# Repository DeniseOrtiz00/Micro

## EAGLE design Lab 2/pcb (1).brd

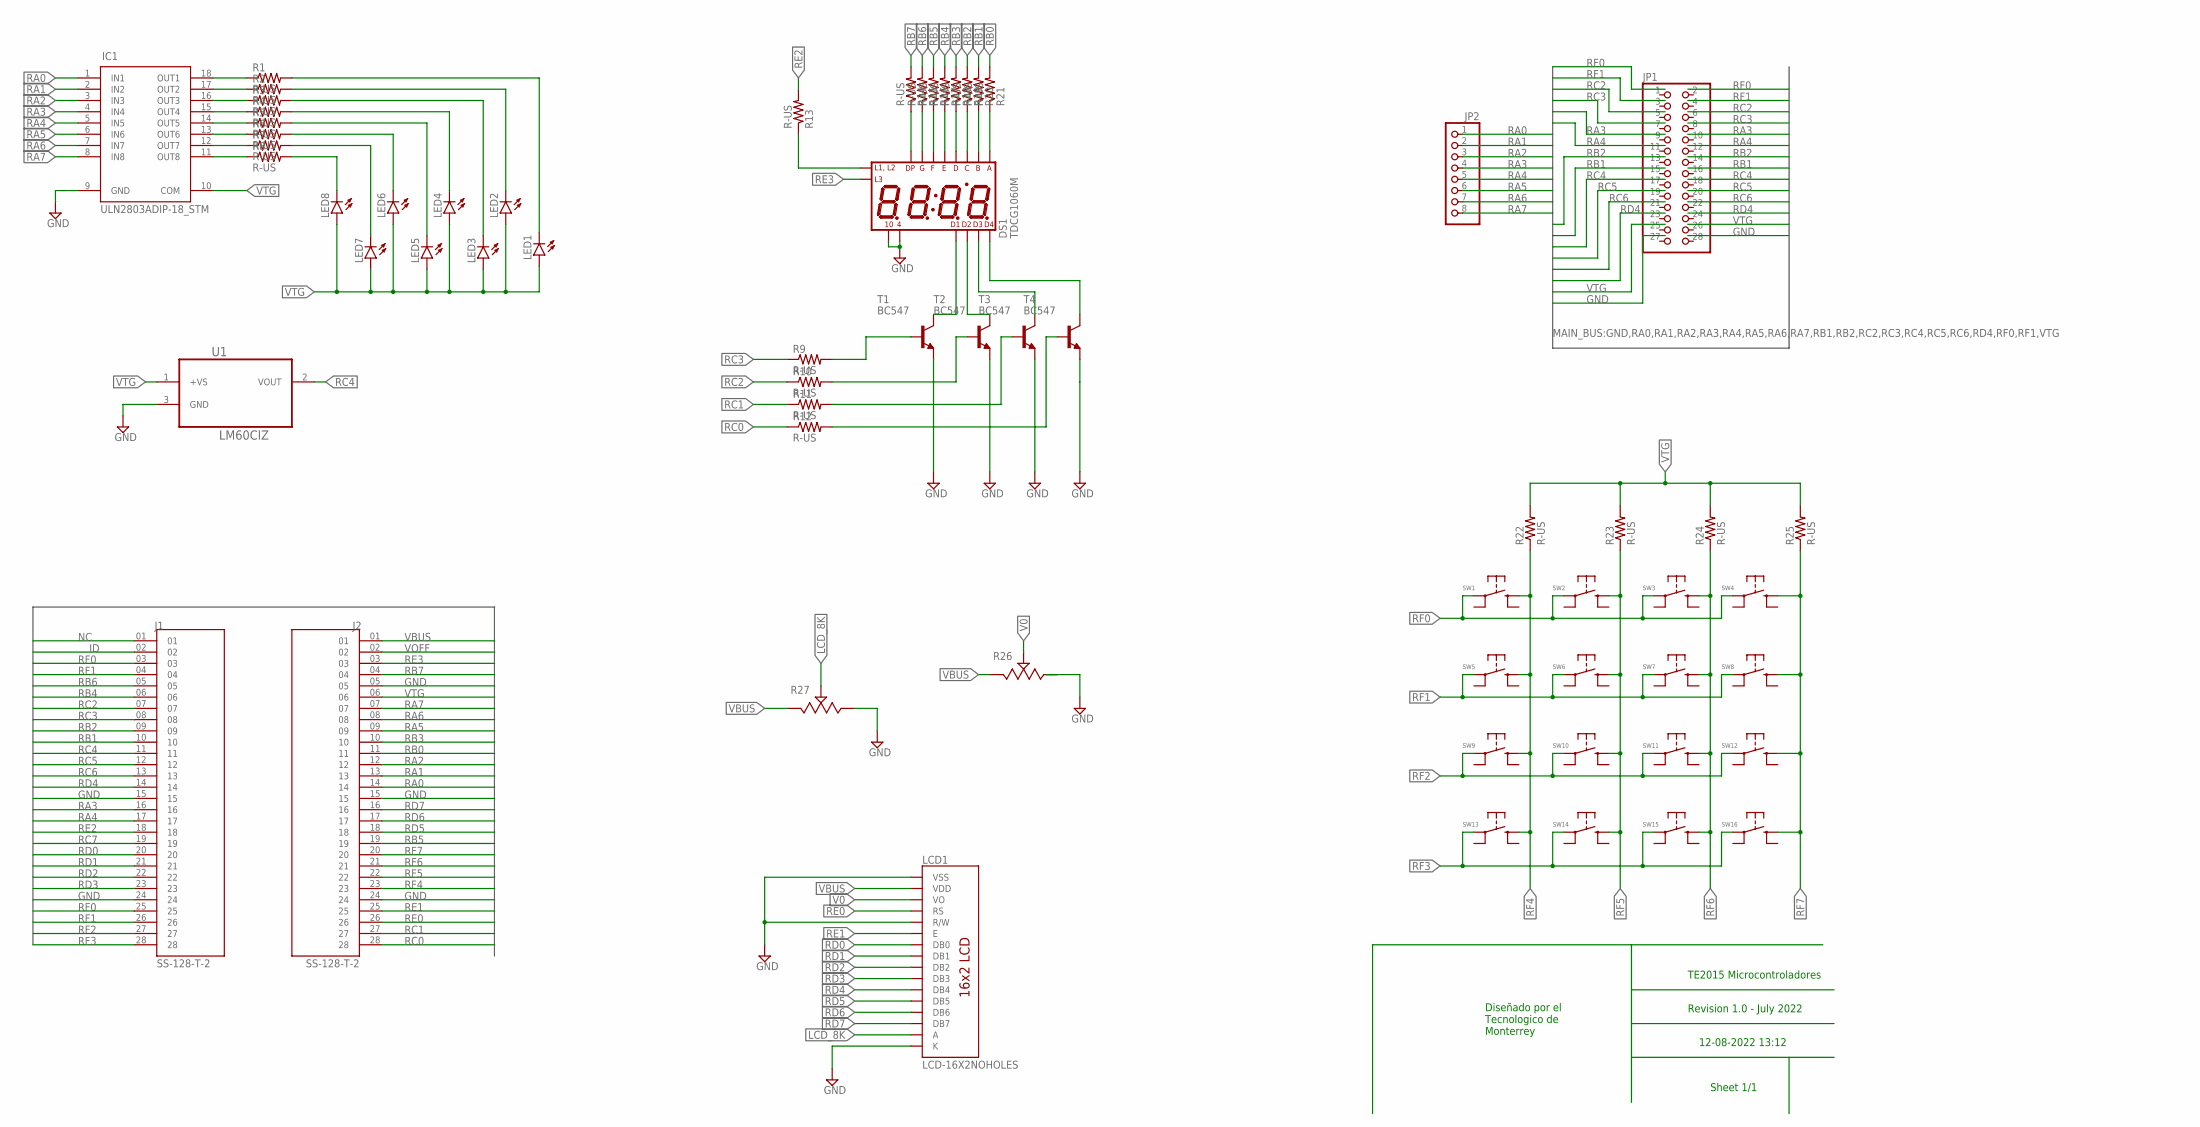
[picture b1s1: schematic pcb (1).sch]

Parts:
DS1: TDCG1060M; DISPLAY_TDCG1060M
IC1: ULN2803ADIP-18_STM; DIP-18_STM
J1, J2: SS-128-T-2; SAMTEC_SS-128-T-2
JP1: PINHD-2X14-CB; 2X14-BIG
JP2: PINHD-1X8BIG; 1X08-BIG
LCD1: LCD-16X2NOHOLES; LCD-16X2_NOHOLESNOSILK
LED1, LED2, LED3, LED4, LED5, LED6, LED7, LED8: LED3MM
R1, R2, R3, R4, R5, R6, R7, R8, R9, R10, R11, R12, R13, R14, R15, R16, R17, R18, R19, R20, R21, R22, R23, R24, R25: R-US; 0207/10
R26, R27: 3362P-1-103LF
SW1, SW2, SW3, SW4, SW5, SW6, SW7, SW8, SW9, SW10, SW11, SW12, SW13, SW14, SW15, SW16: 1825910-2; TE_1825910-2
T1, T2, T3, T4: BC547; TO92
U1: LM60CIZ; TO92/

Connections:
GND: DS1.4, DS1.10, IC1.9 (GND), J1.15, J1.24, J2.05, J2.15, J2.24, LCD1.1 (VSS), LCD1.5 (R/W), LCD1.16 (K), R26.3, R27.3, T1.1 (E), T2.1 (E), T3.1 (E), T4.1 (E), U1.3 (GND)
ID: J1.02
LCD_8K: LCD1.15 (A), R27.2
unnamed: LED8.K (C), R8.2
unnamed: LED7.K (C), R7.2
unnamed: LED6.K (C), R6.2
unnamed: LED5.K (C), R5.2
unnamed: LED4.K (C), R4.2
unnamed: LED3.K (C), R3.2
unnamed: LED2.K (C), R2.2
unnamed: LED1.K (C), R1.2
unnamed: DS1.1 (DIG1), T1.3 (C)
unnamed: IC1.18 (OUT1), R1.1
unnamed: IC1.17 (OUT2), R2.1
unnamed: IC1.16 (OUT3), R3.1
unnamed: IC1.15 (OUT4), R4.1
unnamed: IC1.14 (OUT5), R5.1
unnamed: IC1.13 (OUT6), R6.1
unnamed: IC1.12 (OUT7), R7.1
unnamed: IC1.11 (OUT8), R8.1
unnamed: R9.2, T1.2 (B)
unnamed: R10.2, T2.2 (B)
unnamed: R11.2, T3.2 (B)
unnamed: DS1.2 (DIG2), T2.3 (C)
unnamed: DS1.6 (DIG3), T3.3 (C)
unnamed: DS1.8 (DIG4), T4.3 (C)
unnamed: DS1.7 (DP), R14.1
unnamed: DS1.15 (G), R15.1
unnamed: DS1.11 (F), R16.1
unnamed: DS1.5 (E), R17.1
unnamed: DS1.3 (D), R18.1
unnamed: DS1.13 (C), R19.1
unnamed: DS1.16 (B), R20.1
unnamed: DS1.14 (A), R21.1
unnamed: R12.2, T4.2 (B)
unnamed: DS1.12 (L1_L2), R13.1
NC: J1.01
RA0: IC1.1 (IN1), J2.14, JP2.1
RA1: IC1.2 (IN2), J2.13, JP2.2
RA2: IC1.3 (IN3), J2.12, JP2.3
RA3: IC1.4 (IN4), J1.16, JP2.4
RA4: IC1.5 (IN5), J1.17, JP2.5
RA5: IC1.6 (IN6), J2.09, JP2.6
RA6: IC1.7 (IN7), J2.08, JP2.7
RA7: IC1.8 (IN8), J2.07, JP2.8
RB0: J2.11, R21.2
RB1: J1.10, R20.2
RB2: J1.09, R19.2
RB3: J2.10, R18.2
RB4: J1.06, R17.2
RB5: J2.19, R16.2
RB6: J1.05, R15.2
RB7: J2.04, R14.2
RC0: J2.28, R12.1
RC1: J2.27, R11.1
RC2: J1.07, R10.1
RC3: J1.08, R9.1
RC4: J1.11, U1.2 (VOUT)
RC5: J1.12
RC6: J1.13
RC7: J1.19
RD0: J1.20, LCD1.7 (DB0)
RD1: J1.21, LCD1.8 (DB1)
RD2: J1.22, LCD1.9 (DB2)
RD3: J1.23, LCD1.10 (DB3)
RD4: J1.14, LCD1.11 (DB4)
RD5: J2.18, LCD1.12 (DB5)
RD6: J2.17, LCD1.13 (DB6)
RD7: J2.16, LCD1.14 (DB7)
RE0: J2.26, LCD1.4 (RS)
RE1: J2.25, LCD1.6 (E)
RE2: J1.18, R13.2
RE3: DS1.9 (L3), J2.03
RF0: J1.03, J1.25, SW1.1, SW2.1, SW3.1, SW4.1
RF1: J1.04, J1.26, SW5.1, SW6.1, SW7.1, SW8.1
RF2: J1.27, SW9.1, SW10.1, SW11.1, SW12.1
RF3: J1.28, SW13.1, SW14.1, SW15.1, SW16.1
RF4: J2.23, R22.1, SW1.2 (S), SW5.2 (S), SW9.2 (S), SW13.2 (S)
RF5: J2.22, R23.1, SW2.2 (S), SW6.2 (S), SW10.2 (S), SW14.2 (S)
RF6: J2.21, R24.1, SW3.2 (S), SW7.2 (S), SW11.2 (S), SW15.2 (S)
RF7: J2.20, R25.1, SW4.2 (S), SW8.2 (S), SW12.2 (S), SW16.2 (S)
V0: LCD1.3 (VO), R26.2
VBUS: J2.01, LCD1.2 (VDD), R26.1, R27.1
VOFF: J2.02
VTG: IC1.10 (COM), J2.06, LED1.A, LED2.A, LED3.A, LED4.A, LED5.A, LED6.A, LED7.A, LED8.A, R22.2, R23.2, R24.2, R25.2, U1.1 (+VS)

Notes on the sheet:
Diseñado por el Tecnologico de Monterrey
TE2015 Microcontroladores
Revision 1.0 - July 2022
12-08-2022 13:12
Sheet 1/1

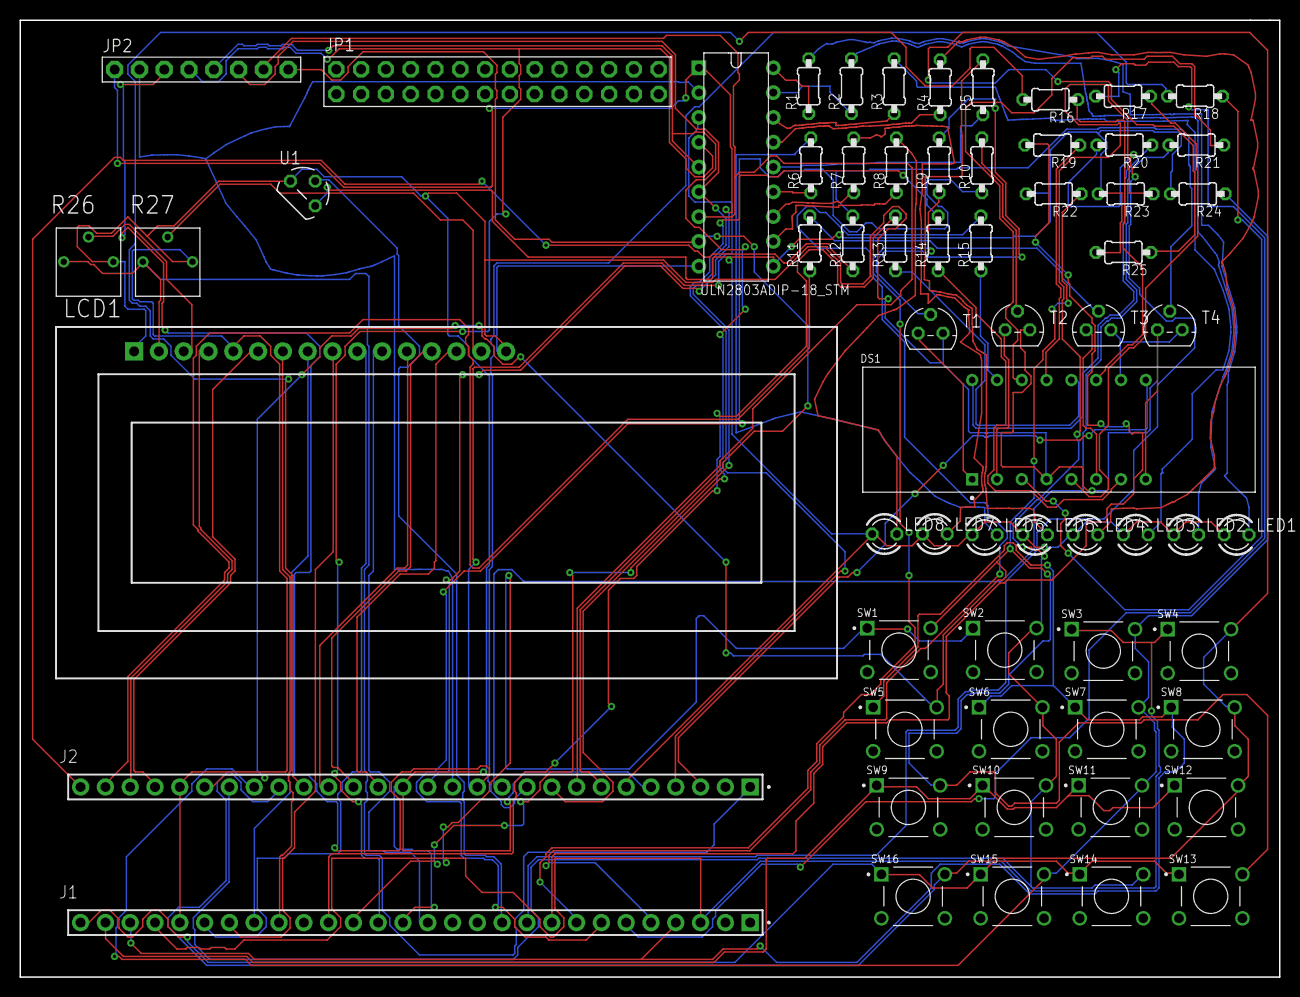
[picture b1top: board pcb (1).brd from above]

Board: 2 copper layers, 129.0 x 98.0 mm, 63 parts (0 on the bottom side), 79 nets.

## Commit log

2022-08-30 Create Lab 2
2022-08-30 Update Lab 2
2022-09-05 Create Lab 3

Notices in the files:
parts and their libraries:
COPYRIGHT: Copyright (C) 2022 Ultra Librarian. All rights reserved.
